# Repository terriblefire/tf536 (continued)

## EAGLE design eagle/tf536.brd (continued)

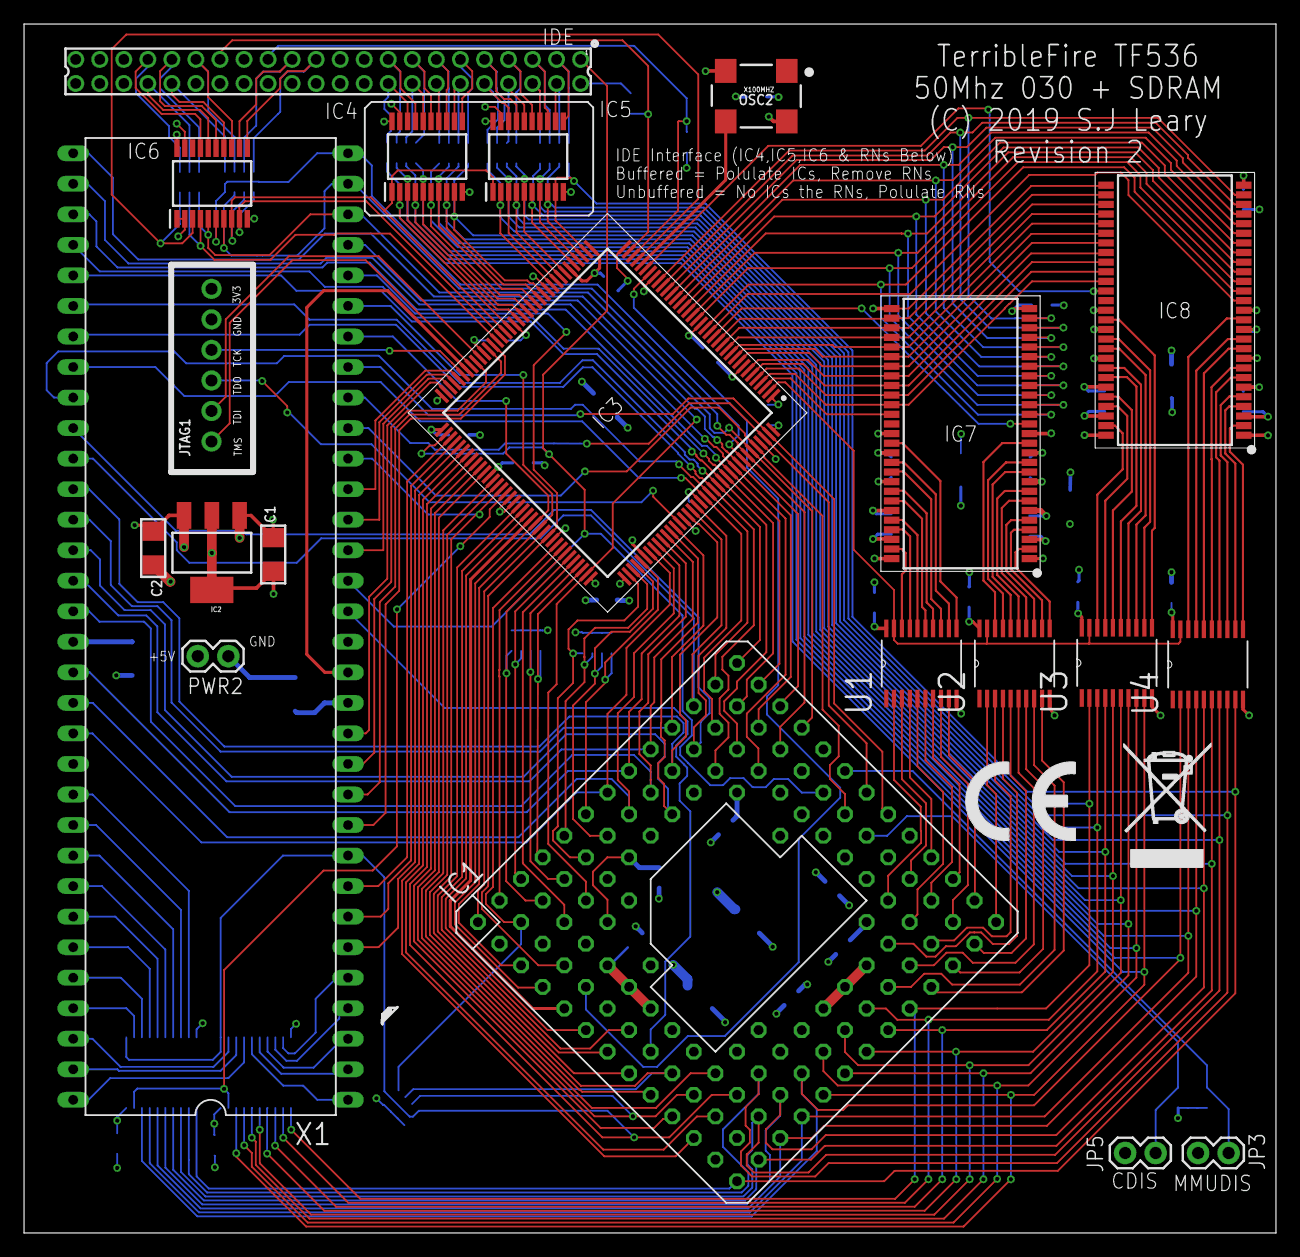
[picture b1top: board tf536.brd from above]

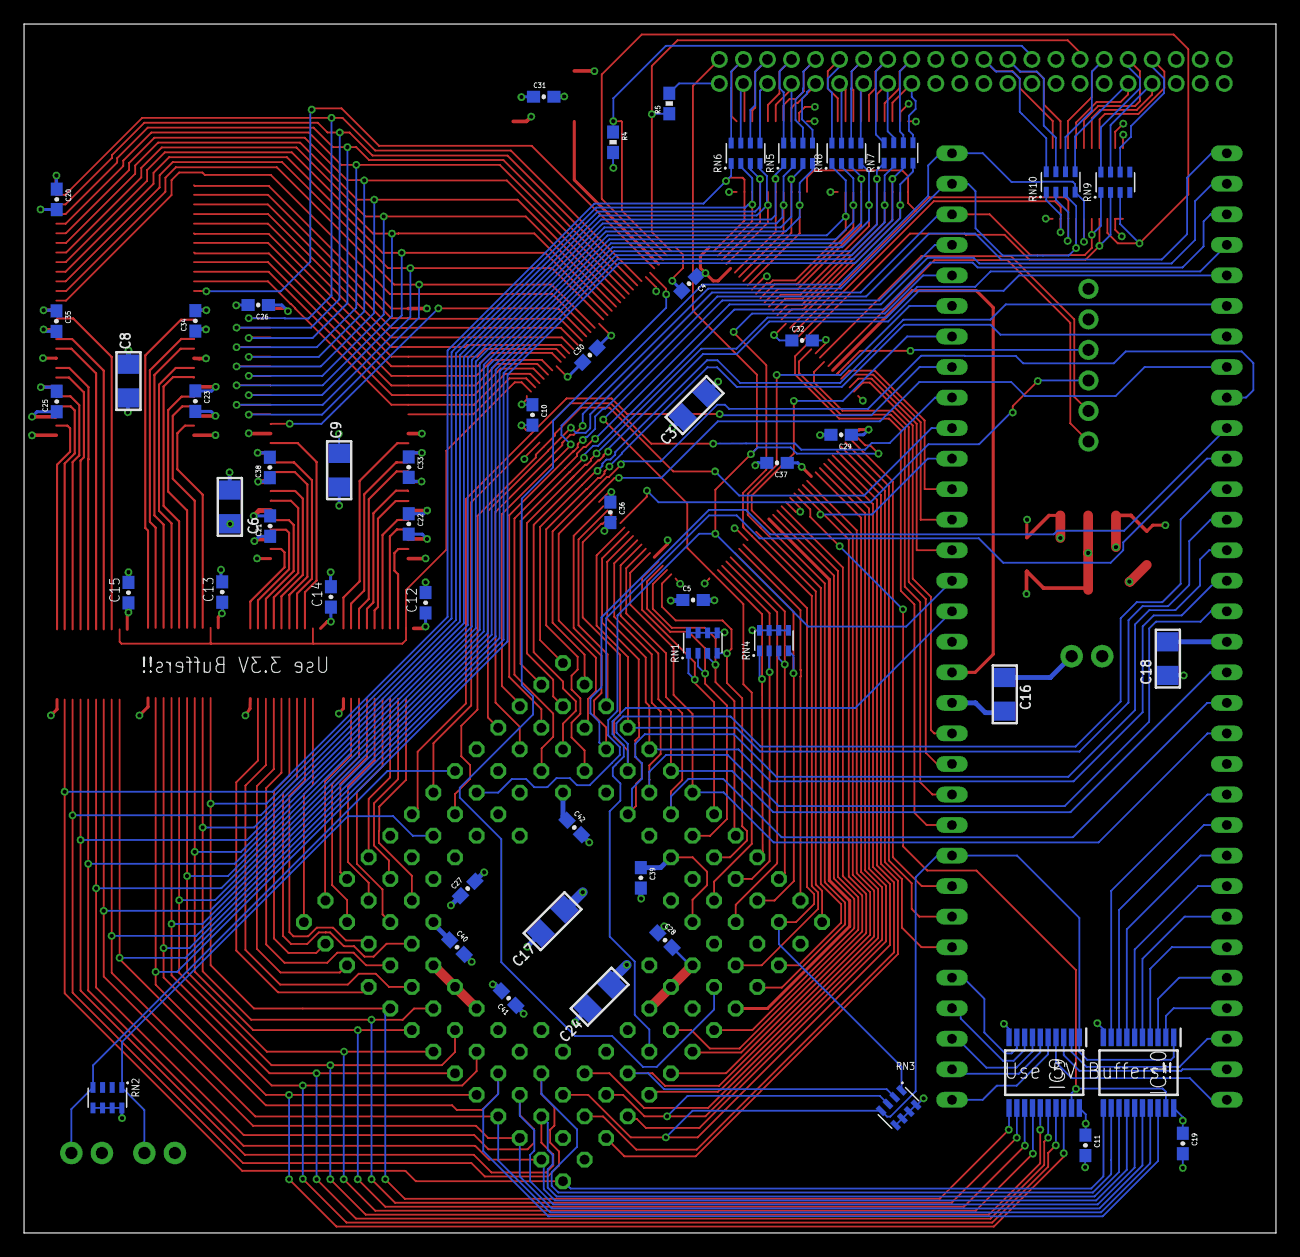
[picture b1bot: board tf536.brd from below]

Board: 4 copper layers, 104.1 x 100.6 mm, 74 parts (53 on the bottom side), 214 nets.

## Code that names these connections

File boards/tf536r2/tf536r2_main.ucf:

# Copyright (C) 2016-2017, Stephen J. Leary
# All rights reserved.
#
# This file is part of TF530 (Terrible Fire 030 Accelerator)
#
# TF536 is free software: you can redistribute it and/or modify
# it under the terms of the GNU General Public License as published by
# the Free Software Foundation, either version 3 of the License, or
# (at your option) any later version.
#
# TF530 is distributed in the hope that it will be useful,
# but WITHOUT ANY WARRANTY; without even the implied warranty of
# MERCHANTABILITY or FITNESS FOR A PARTICULAR PURPOSE.  See the
# GNU General Public License for more details.
#
# You should have received a copy of the GNU General Public License
# along with TF530. If not, see <http://www.gnu.org/licenses/>.

NET "A<0>"      LOC="101";
NET "A<1>"      LOC="107";
NET "A<2>"      LOC="139";
NET "A<3>"      LOC="138";
NET "A<4>"      LOC="137";
NET "A<5>"      LOC="136";
NET "A<6>"      LOC="135";
NET "A<7>"      LOC="134";
NET "A<8>"      LOC="133";
NET "A<9>"      LOC="132";
NET "A<10>"      LOC="131";
NET "A<11>"      LOC="130";
NET "A<12>"      LOC="128";
NET "A<13>"      LOC="129";
NET "A<14>"      LOC="126";
NET "A<15>"      LOC="125";
NET "A<16>"      LOC="124";
NET "A<17>"      LOC="121";
NET "A<18>"      LOC="120";
NET "A<19>"      LOC="119";
NET "A<20>"      LOC="118";
NET "A<21>"      LOC="117";
NET "A<22>"      LOC="116";
NET "A<23>"      LOC="115";
NET "A<24>"      LOC="113";
NET "A<25>"      LOC="112";
NET "A<26>"      LOC="111";
NET "A<27>"      LOC="110";
NET "A<28>"      LOC="106";
NET "A<29>"      LOC="105";
NET "A<30>"      LOC="103";
NET "A<31>"      LOC="102";
NET "ARAM<0>"      LOC="25";
NET "ARAM<1>"      LOC="26";
NET "ARAM<2>"      LOC="27";
NET "ARAM<3>"      LOC="28";
NET "ARAM<4>"      LOC="14";
NET "ARAM<5>"      LOC="13";
NET "ARAM<6>"      LOC="12";
NET "ARAM<7>"      LOC="11";
NET "ARAM<8>"      LOC="10";
NET "ARAM<9>"      LOC="9";
NET "ARAM<10>"      LOC="24";
NET "ARAM<11>"      LOC="7";
NET "ARAM<12>"      LOC="6";
NET "AS"      LOC="77";
NET "AS30"      LOC="86";
NET "AVEC"      LOC="30";
NET "BA<0>"      LOC="23";
NET "BA<1>"      LOC="22";
NET "BERR"      LOC="87";
NET "BG"      LOC="61";
NET "BG30"      LOC="100";
NET "BGACK"      LOC="64";
NET "BGACK30"      LOC="104";
NET "BR"      LOC="71";
NET "BR30"      LOC="97";
NET "BUSEN"      LOC="88";
NET "CAS"      LOC="19";
NET "CBACK"      LOC="85";
NET "CBREQ"      LOC="81";
NET "CIIN"      LOC="78";
NET "CLK7M_RAW"      LOC="66";
NET "CLK100M"      LOC="32";
NET "CLKCPU"      LOC="94";
NET "CLKRAM"      LOC="4";
NET "CLKRAME"      LOC="5";
NET "D<0>"      LOC="39";
NET "D<1>"      LOC="41";
NET "D<2>"      LOC="44";
NET "D<3>"      LOC="46";
NET "D<4>"      LOC="49";
NET "D<5>"      LOC="51";
NET "D<6>"      LOC="53";
NET "D<7>"      LOC="56";
NET "D<8>"      LOC="54";
NET "D<9>"      LOC="52";
NET "D<10>"      LOC="50";
NET "D<11>"      LOC="48";
NET "D<12>"      LOC="45";
NET "D<13>"      LOC="43";
NET "D<14>"      LOC="40";
NET "D<15>"      LOC="38";
NET "DQM<3>"      LOC="16";
NET "DQM<2>"      LOC="31";
NET "DQM<1>"      LOC="15";
NET "DQM<0>"      LOC="3";
NET "DS30"      LOC="82";
NET "DSACK<0>"      LOC="93";
NET "DSACK<1>"      LOC="92";
NET "DTACK"      LOC="60";
NET "E"      LOC="69";
NET "FC<0>"      LOC="98";
NET "FC<1>"      LOC="96";
NET "FC<2>"      LOC="95";
NET "IDECS<0>"      LOC="33";
NET "IDECS<1>"      LOC="59";
NET "IDEINT"      LOC="35";
#NET "IDEWAIT"      LOC="34";
NET "IOR"      LOC="57";
NET "IOW"      LOC="58";
NET "IPL<0>"      LOC="143";
NET "IPL<1>"      LOC="142";
NET "IPL<2>"      LOC="140";
NET "LDS"      LOC="75";
NET "RAMCS"      LOC="21";
NET "RAMOE"      LOC="2";
NET "RAMWE"      LOC="17";
NET "RAS"      LOC="20";
NET "RESET"      LOC="74";
NET "RW30"      LOC="80";
NET "SIZ<0>"      LOC="79";
NET "SIZ<1>"      LOC="83";
NET "STERM"      LOC="91";
NET "UDS"      LOC="76";
NET "VMA"      LOC="70";
NET "VPA"      LOC="68";

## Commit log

2025-11-16 Initial commit - TF536 68030 Accelerator
    Complete TF536 project with:
    - CPLD firmware (Verilog RTL) for Amiga 500 and CDTV
    - 68k assembly boot ROM
    - Eagle CAD hardware design files (4-layer PCB)
    - Automated build system with Docker support
    - GitHub Actions CI/CD workflows
2025-11-16 Add release workflow for automated package creation
    - Build CPLD firmware for both A500 and CDTV
    - Generate Gerbers, BOM, CPL, and schematic PDF
    - Create structured release package with firmware, pcb, assembly, and docs
    - Include all documentation (README, LICENSE, IDE options, JLCPCB guide)
    - Automated release creation on version tags
    - Manual trigger via workflow_dispatch
2025-11-16 Update JLCPCB ordering guide for TF536
    - Replace all TFMSX references with TF536
    - Update repository URLs to tf536
    - Update file naming examples (tf536_bom.csv, tf536_cpl.csv, etc.)
    - Add IDE interface build options warning
    - Update firmware description to mention A500 and CDTV variants
2025-11-16 Build both XC95144XL and XC95288XL variants for each platform
    - Update Makefile to build both CPLD sizes (144 and 288) for A500 and CDTV
    - Add individual build targets: a500-144, a500-288, cdtv-144, cdtv-288
    - Default 'make a500' and 'make cdtv' now build both chip variants
    - Update README to document all four firmware variants
    - Add note recommending XC95288XL (FULL) for most builds
    - Total of 4 JED files per build: A500/CDTV × 144/288
2025-11-16 Replace FULL variable with more descriptive CHIPSIZE
    - Rename FULL=0/1 to CHIPSIZE=144/288 for better readability
    - Update JED file naming from _FULL to _XC95144XL/_XC95288XL
    - Makes it immediately clear which CPLD chip size is being built
    - Update all documentation to reflect new naming scheme
    - More intuitive: CHIPSIZE=288 vs FULL=1
2025-11-16 Fix make clean to properly remove all build artifacts
    - Update Makefile.cpld to remove *.jed and *.svf files
    - Add clean and distclean targets to tf536r2/Makefile
    - Remove xlnx_auto_* temporary files
    - Ensure work directories, JED files, SVF files are all cleaned
    - Fix issue where JED files were not being removed by make clean
2025-11-16 Fix make clean to properly remove JED and SVF files
    - Move *.jed and *.svf removal from distclean to clean target
    - Remove duplicate clean/distclean targets from tf536r2/Makefile
    - distclean now only removes backup files (*~)
    - Resolves issue where 'make clean' was not removing JED files
2025-11-16 Make XC95144XL builds manual only, default to XC95288XL
    - Default 'make a500' and 'make cdtv' now only build XC95288XL variant
    - XC95144XL builds (144) are manual only via explicit targets
    - Update README to clarify XC95288XL is recommended default
    - Note that XC95144XL design may not fit
    - Reduces build time by only building recommended variant
    - Users can still manually build 144 variant if needed
2025-11-16 Remove XC95144XL variant references from README
    The BOM requires XC95288XL, so remove all documentation of the 144 variant to avoid confusion.
2025-11-16 Updating the schematic to say XC95288XL
2025-11-16 Add Eagle netlist and UCF generation tools
    - Add generate_netlist.py to export Eagle schematic to netlist format
    - Add generate_ucf.py to generate UCF files from Eagle netlists
    - Filters power (GND, VCC) and JTAG (TCK/TDI/TDO/TMS) signals
    - Handles 68030-specific signals (AS30, BG30, etc.) correctly
    - Optional --remap-dbus flag to map D16-D31 to D<0>-D<15>
    - Update Eagle schematic signal names to match UCF conventions:
2025-12-29 update discord link to non expiring one
